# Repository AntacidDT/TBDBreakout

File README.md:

## Breakout for the TBD62003APG Board
This board is licensed CERN-OHL-S, and is meant to be a breakout PCB board for
the TBD62003APG to 28BYJ-48 stepper motor.

## License
This board may be used freely, but if distributed or modified it should be licensed as CERN-OHL-S aswell.
You should've been given a copy of the [License](LICENSE.txt) with this repository.

## Why did I make this
I made this because even tho the ULN2003A Breakout PCB's are good, the TBD62003APG is a
lot more efficient, thus I figured a breakout made for TBD62003APG could be very useful for everyone.

## Where to get the PCB gerbers
A Zip folder is found at [/pcbgerbers/tbd62003apg_gerbers.zip](/pcbgerbers/tbd62003apg_gerbers.zip), and if you want the raw PCB gerber files, its found at [/pcbgerbers/rawpcbgerbers](/pcbgerbers/rawpcbgerbers/). The PCB gerbers use Protel Filenames because many PCB manufacturers recommend and highly prefer Protel Filename Extensions instead.

## Thanks for reading :))
Also this repository is often short for what I do, but I released this to github purely to share it to the community for free and make a positive impact.

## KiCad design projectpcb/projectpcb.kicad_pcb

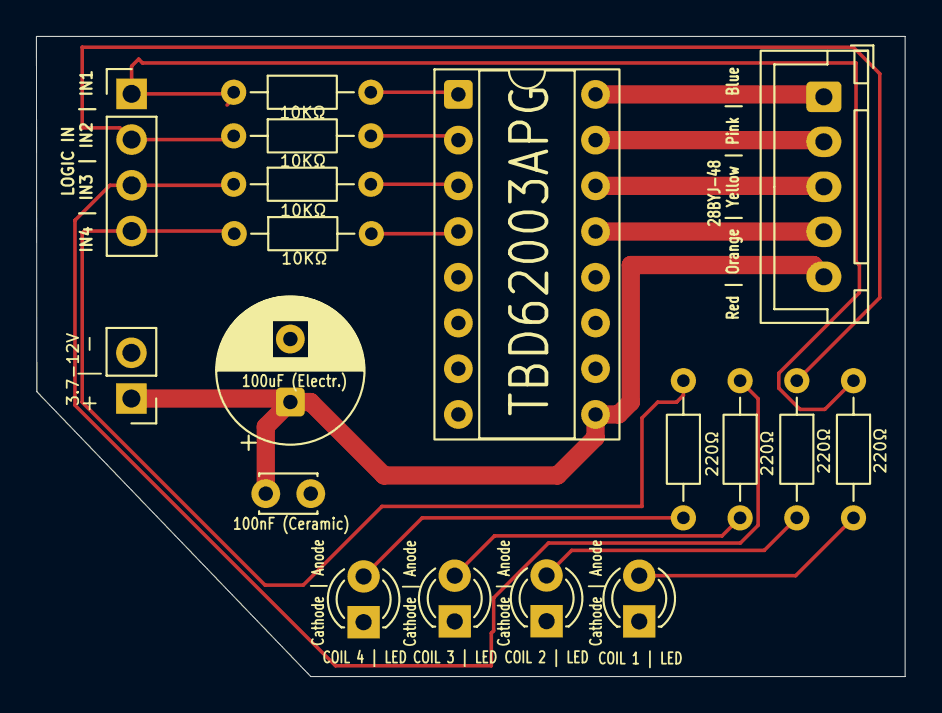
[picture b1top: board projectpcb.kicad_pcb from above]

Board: 2 copper layers, 48.3 x 35.6 mm, 18 parts (0 on the bottom side), 18 nets.

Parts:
C1: Electrolytic; CP_Radial_D8.0mm_P3.50mm
C2: Ceramic; C_Disc_D3.0mm_W2.0mm_P2.50mm
D1, D2, D3, D4: LED; LED_D3.0mm
J1: TBD62003APG; DIP-16_W7.62mm_Socket
J2: PWR; PinHeader_1x02_P2.54mm_Vertical
J3: LOGIC-IN; PinHeader_1x04_P2.54mm_Vertical
J4: LOGIC-OUT; JST_XH_B5B-XH-A_1x05_P2.50mm_Vertical
R1|10k1, R2|10k1, R3|10k1, R4|10k1, R5|220, R6|220, R7|220, R8|220: R; R_Axial_DIN0204_L3.6mm_D1.6mm_P7.62mm_Horizontal

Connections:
+4V: C1.1, C2.2, J1.9, J2.1, J4.5
GND: C1.2, C2.1, D1.1 (K), D2.1 (K), D3.1 (K), D4.1 (K), J1.5, J1.6, J1.7, J1.8, J2.2
IN1: J3.1, R1|10k1.1, R5|220.1
IN2: J3.2, R2|10k1.1, R6|220.1
IN3: J3.3, R3|10k1.1, R7|220.1
IN4: J3.4, R4|10k1.1, R8|220.1
unnamed: D1.2 (A), R5|220.2
unnamed: D2.2 (A), R6|220.2
unnamed: D3.2 (A), R7|220.2
unnamed: D4.2 (A), R8|220.2
unnamed: J1.1, R1|10k1.2
unnamed: J1.2, R2|10k1.2
unnamed: J1.3, R3|10k1.2
unnamed: J1.4, R4|10k1.2
unnamed: J1.13, J4.4
unnamed: J1.14, J4.3
unnamed: J1.15, J4.2
unnamed: J1.16, J4.1

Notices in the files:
projectpcb/projectpcb.kicad_pcb:
be licensed CERN-OHL-S if
License: CERN-OHL-S
